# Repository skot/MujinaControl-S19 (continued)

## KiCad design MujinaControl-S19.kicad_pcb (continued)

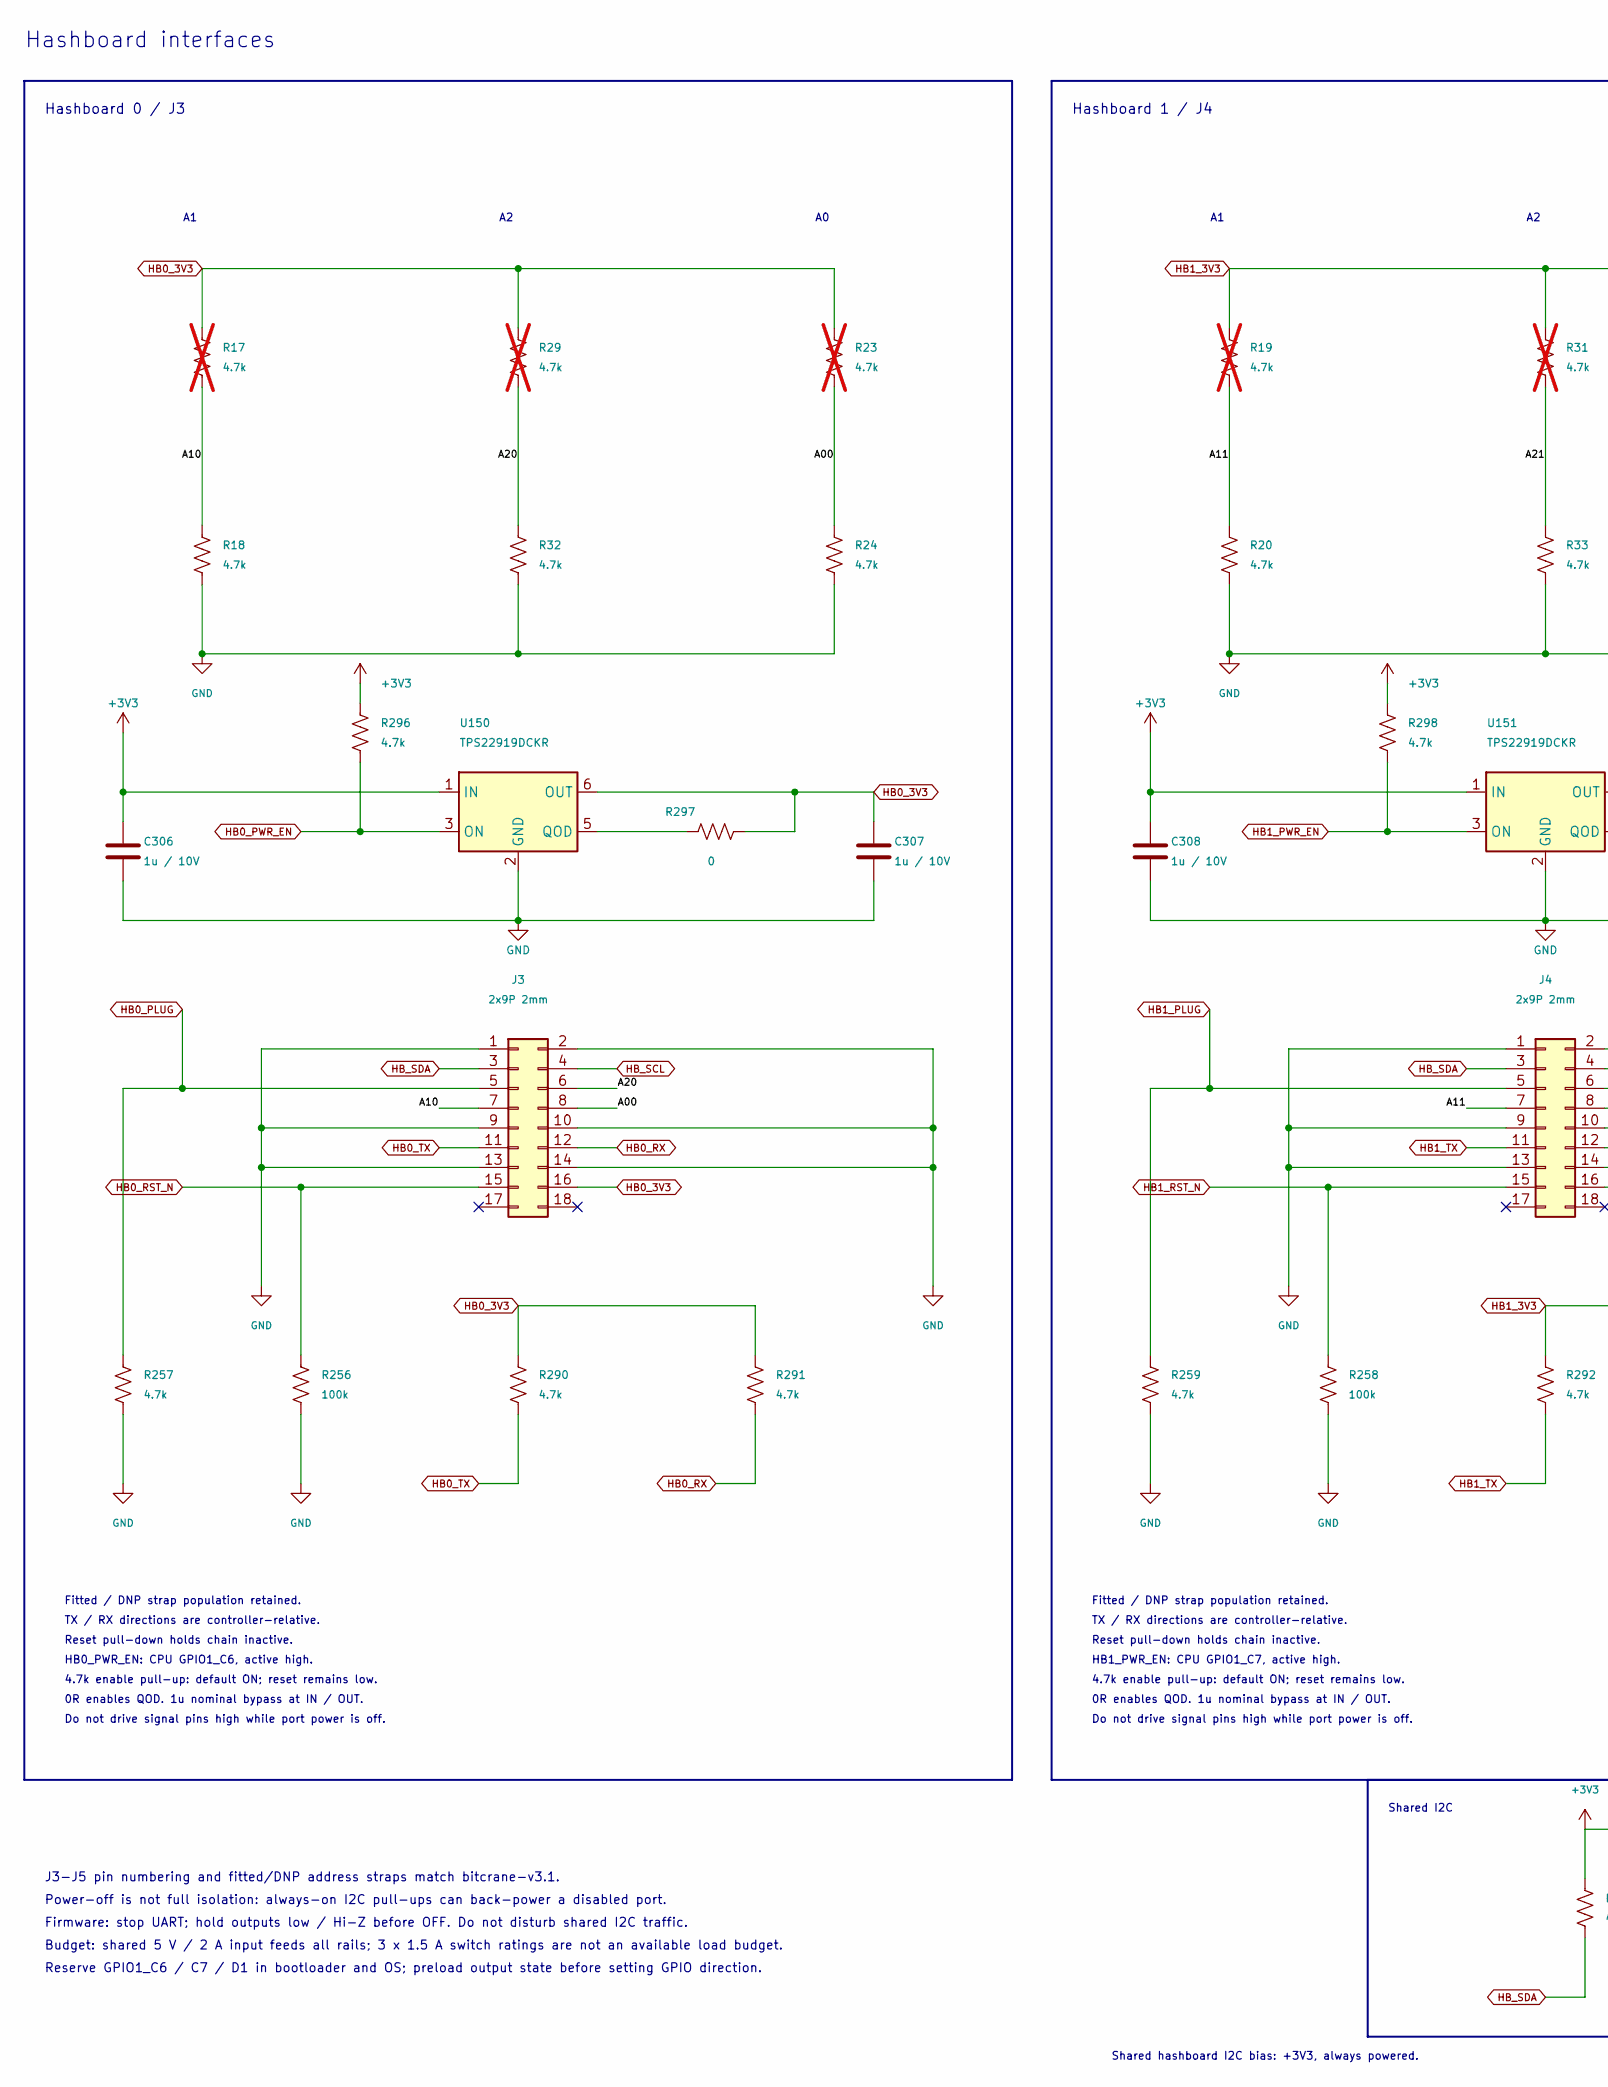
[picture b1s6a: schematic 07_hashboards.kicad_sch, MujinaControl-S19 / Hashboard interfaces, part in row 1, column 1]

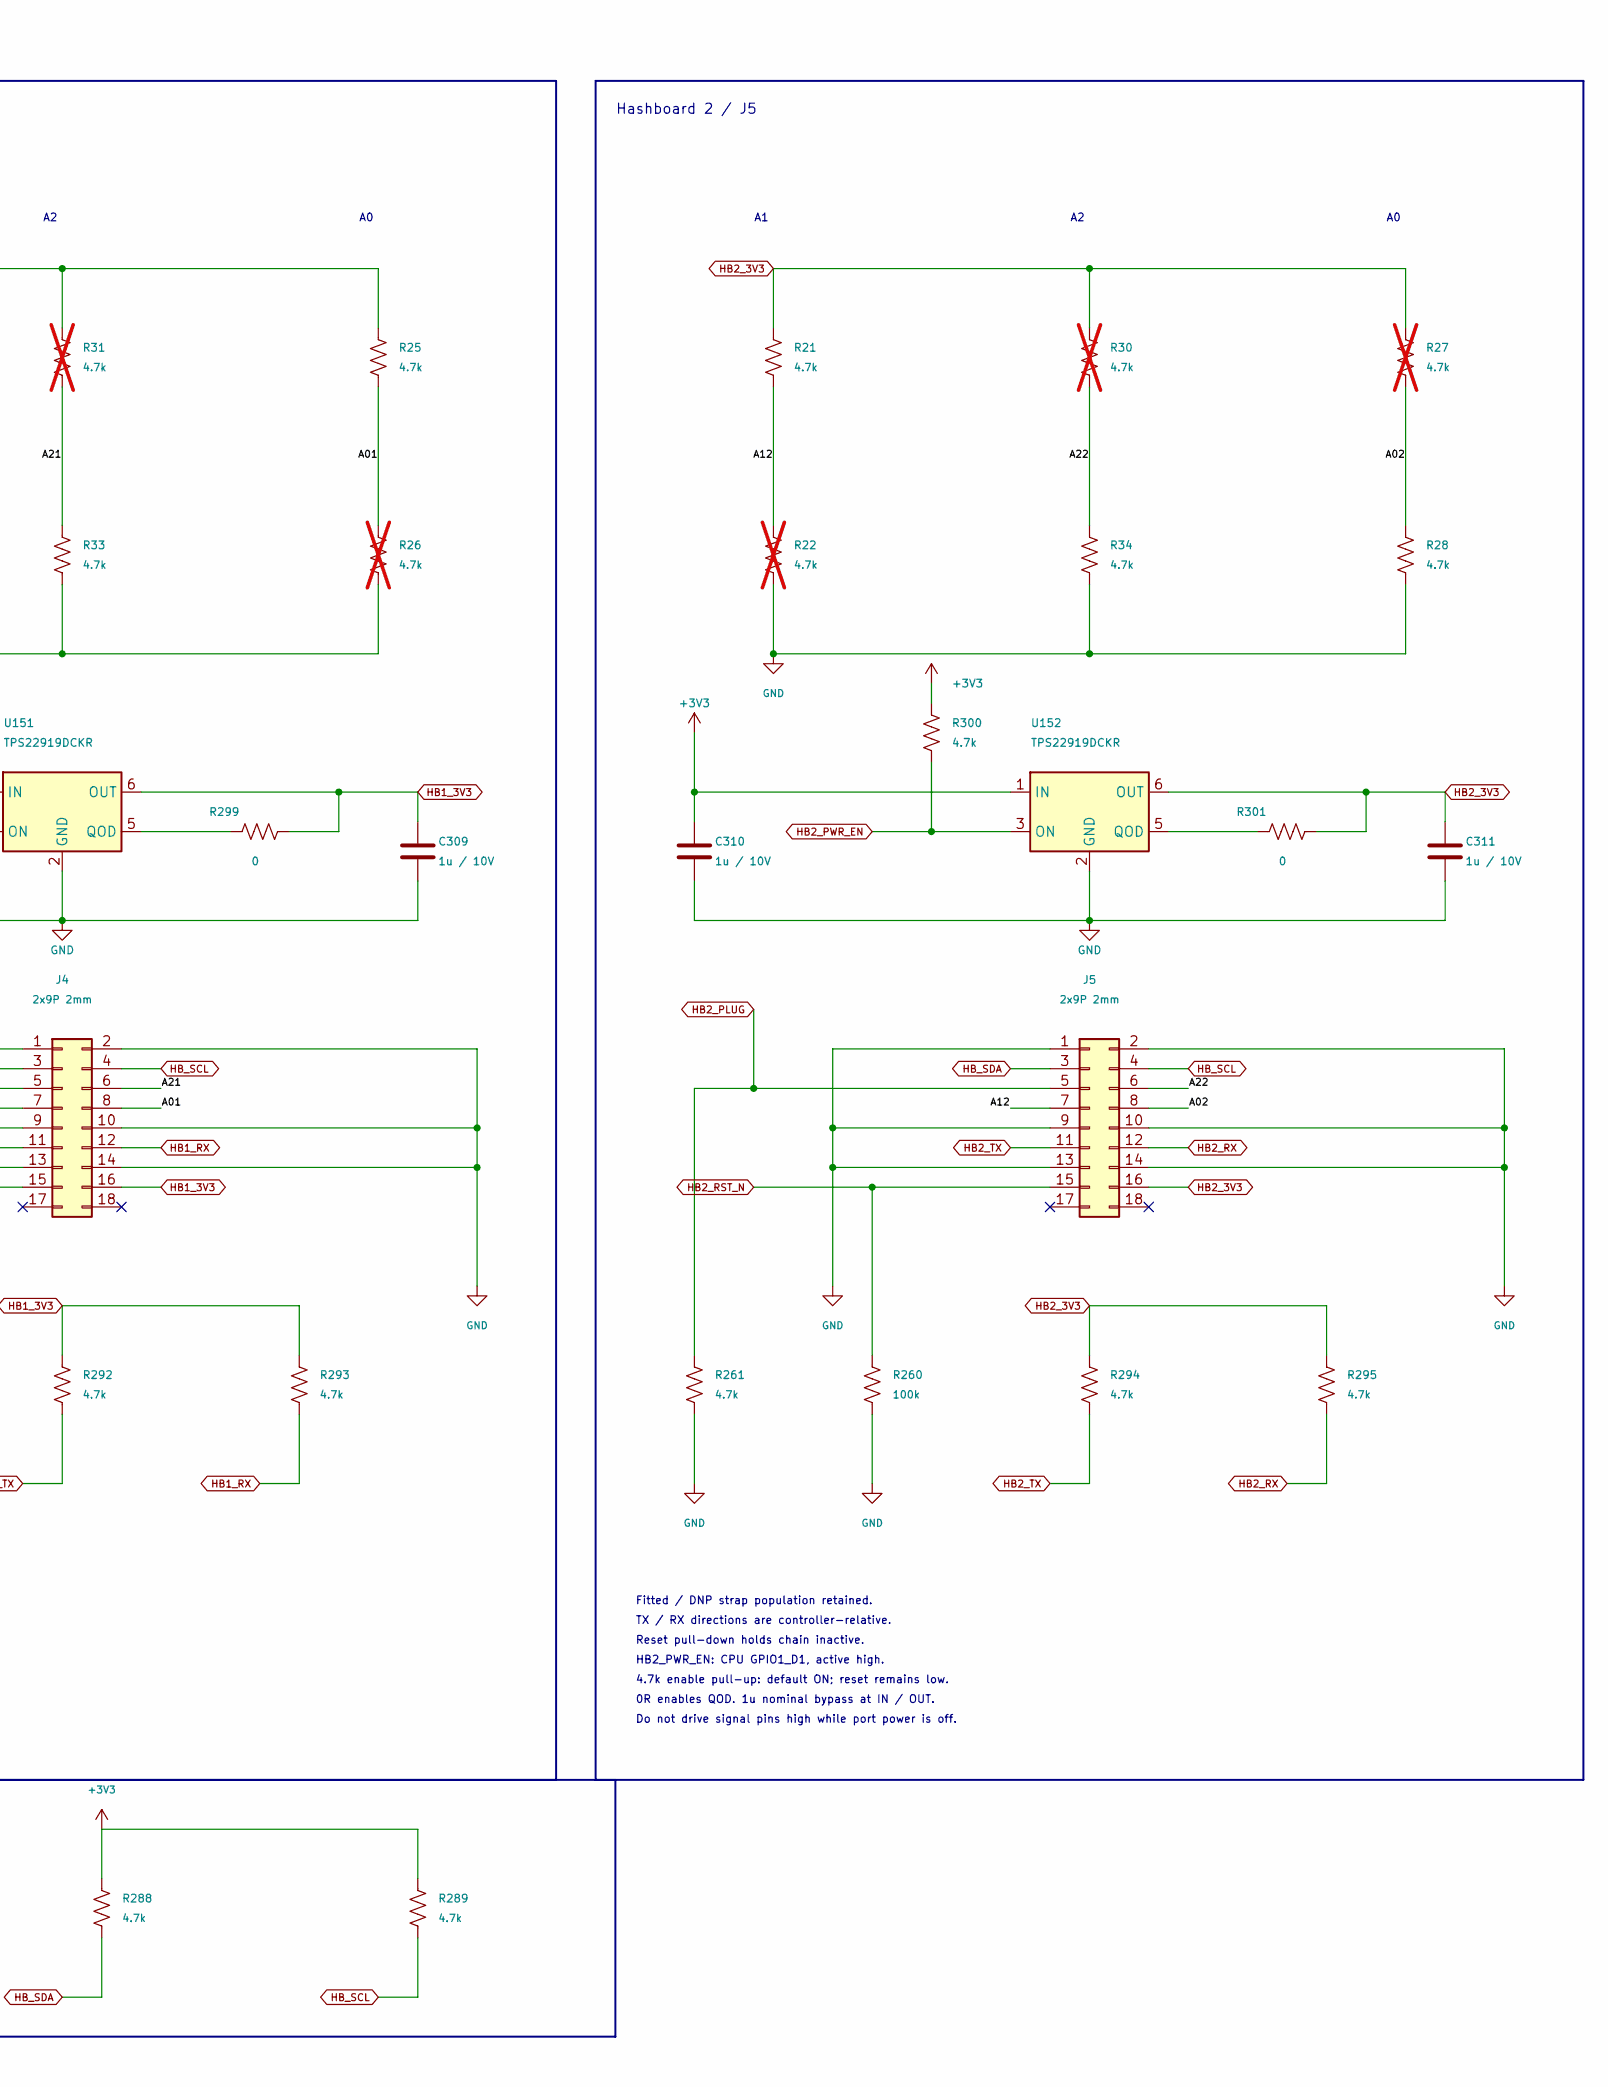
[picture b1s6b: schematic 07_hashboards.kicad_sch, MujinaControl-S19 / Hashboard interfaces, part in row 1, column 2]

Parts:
C306, C307, C308, C309, C310, C311: 1u / 10V; C_0402_1005Metric; MPN CL05A105KA5NQNC; LCSC C52923
J3, J4, J5: 2x9P 2mm; CONN-TH_X2026WV-2-09D-46SN; MPN X2026WV-2x09D-46SN; LCSC C437089
R17, R19, R22, R23, R26, R27, R29, R30, R31: 4.7k; R_0402_1005Metric; MPN 0402WGF4701TCE; LCSC C25900; not fitted
R18, R20, R21, R24, R25, R28, R32, R33, R34, R257, R259, R261, R288, R289, R290, R291, R292, R293, R294, R295, R296, R298, R300: 4.7k; R_0402_1005Metric; MPN 0402WGF4701TCE; LCSC C25900
R256, R258, R260: 100k; R_0402_1005Metric; MPN 0402WGF1003TCE; LCSC C25741
R297, R299, R301: 0; R_0402_1005Metric; MPN 0402WGF0000TCE; LCSC C17168
U150, U151, U152: TPS22919DCKR; SOT-363_SC-70-6; MPN TPS22919DCKR; LCSC C2149796

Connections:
+3V3: C306.1, C308.1, C310.1, R288.1, R289.1, R296.1, R298.1, R300.1, U150.1 (IN), U151.1 (IN), U152.1 (IN); also elsewhere on the board
/Three hashboard interfaces/A00: J3.8, R23.2, R24.1
/Three hashboard interfaces/A01: J4.8, R25.2, R26.1
/Three hashboard interfaces/A02: J5.8, R27.2, R28.1
/Three hashboard interfaces/A10: J3.7, R17.2, R18.1
/Three hashboard interfaces/A11: J4.7, R19.2, R20.1
/Three hashboard interfaces/A12: J5.7, R21.2, R22.1
/Three hashboard interfaces/A20: J3.6, R29.2, R32.1
/Three hashboard interfaces/A21: J4.6, R31.2, R33.1
/Three hashboard interfaces/A22: J5.6, R30.2, R34.1
GND: C306.2, C307.2, C308.2, C309.2, C310.2, C311.2, J3.1, J3.2, J3.9, J3.10, J3.13, J3.14, J4.1, J4.2, J4.9, J4.10, J4.13, J4.14, J5.1, J5.2, J5.9, J5.10, J5.13, J5.14, R18.2, R20.2, R22.2, R24.2, R26.2, R28.2, R32.2, R33.2, R34.2, R256.2, R257.2, R258.2, R259.2, R260.2, R261.2, U150.2 (GND), U151.2 (GND), U152.2 (GND); also elsewhere on the board
HB0_3V3: C307.1, J3.16, R17.1, R23.1, R29.1, R290.1, R291.1, R297.2, U150.6 (OUT)
HB0_PLUG: J3.5, R257.1; also elsewhere on the board
HB0_PWR_EN: R296.2, U150.3 (ON); also elsewhere on the board
HB0_RST_N: J3.15, R256.1; also elsewhere on the board
HB0_RX: J3.12, R291.2; also elsewhere on the board
HB0_TX: J3.11, R290.2; also elsewhere on the board
HB1_3V3: C309.1, J4.16, R19.1, R25.1, R31.1, R292.1, R293.1, R299.2, U151.6 (OUT)
HB1_PLUG: J4.5, R259.1; also elsewhere on the board
HB1_PWR_EN: R298.2, U151.3 (ON); also elsewhere on the board
HB1_RST_N: J4.15, R258.1; also elsewhere on the board
HB1_RX: J4.12, R293.2; also elsewhere on the board
HB1_TX: J4.11, R292.2; also elsewhere on the board
HB2_3V3: C311.1, J5.16, R21.1, R27.1, R30.1, R294.1, R295.1, R301.2, U152.6 (OUT)
HB2_PLUG: J5.5, R261.1; also elsewhere on the board
HB2_PWR_EN: R300.2, U152.3 (ON); also elsewhere on the board
HB2_RST_N: J5.15, R260.1; also elsewhere on the board
HB2_RX: J5.12, R295.2; also elsewhere on the board
HB2_TX: J5.11, R294.2; also elsewhere on the board
HB_SCL: J3.4, J4.4, J5.4, R289.2; also elsewhere on the board
HB_SDA: J3.3, J4.3, J5.3, R288.2; also elsewhere on the board
unnamed: R297.1, U150.5 (QOD)
unnamed: R299.1, U151.5 (QOD)
unnamed: R301.1, U152.5 (QOD)

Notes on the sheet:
Fitted / DNP strap population retained.
Hashboard 1 / J4
Reset pull-down holds chain inactive.
HB0_PWR_EN: CPU GPIO1_C6, active high.
Power-off is not full isolation: always-on I2C pull-ups can back-power a disabled port.
TX / RX directions are controller-relative.
Do not drive signal pins high while port power is off.
HB1_PWR_EN: CPU GPIO1_C7, active high.
J3-J5 pin numbering and fitted/DNP address straps match bitcrane-v3.1.
4.7k enable pull-up: default ON; reset remains low.
0R enables QOD. 1u nominal bypass at IN / OUT.
Hashboard 0 / J3
Shared I2C
Hashboard 2 / J5
Hashboard interfaces
HB2_PWR_EN: CPU GPIO1_D1, active high.
Budget: shared 5 V / 2 A input feeds all rails; 3 x 1.5 A switch ratings are not an available load budget.
Reserve GPIO1_C6 / C7 / D1 in bootloader and OS; preload output state before setting GPIO direction.
Firmware: stop UART; hold outputs low / Hi-Z before OFF. Do not disturb shared I2C traffic.
Shared hashboard I2C bias: +3V3, always powered.

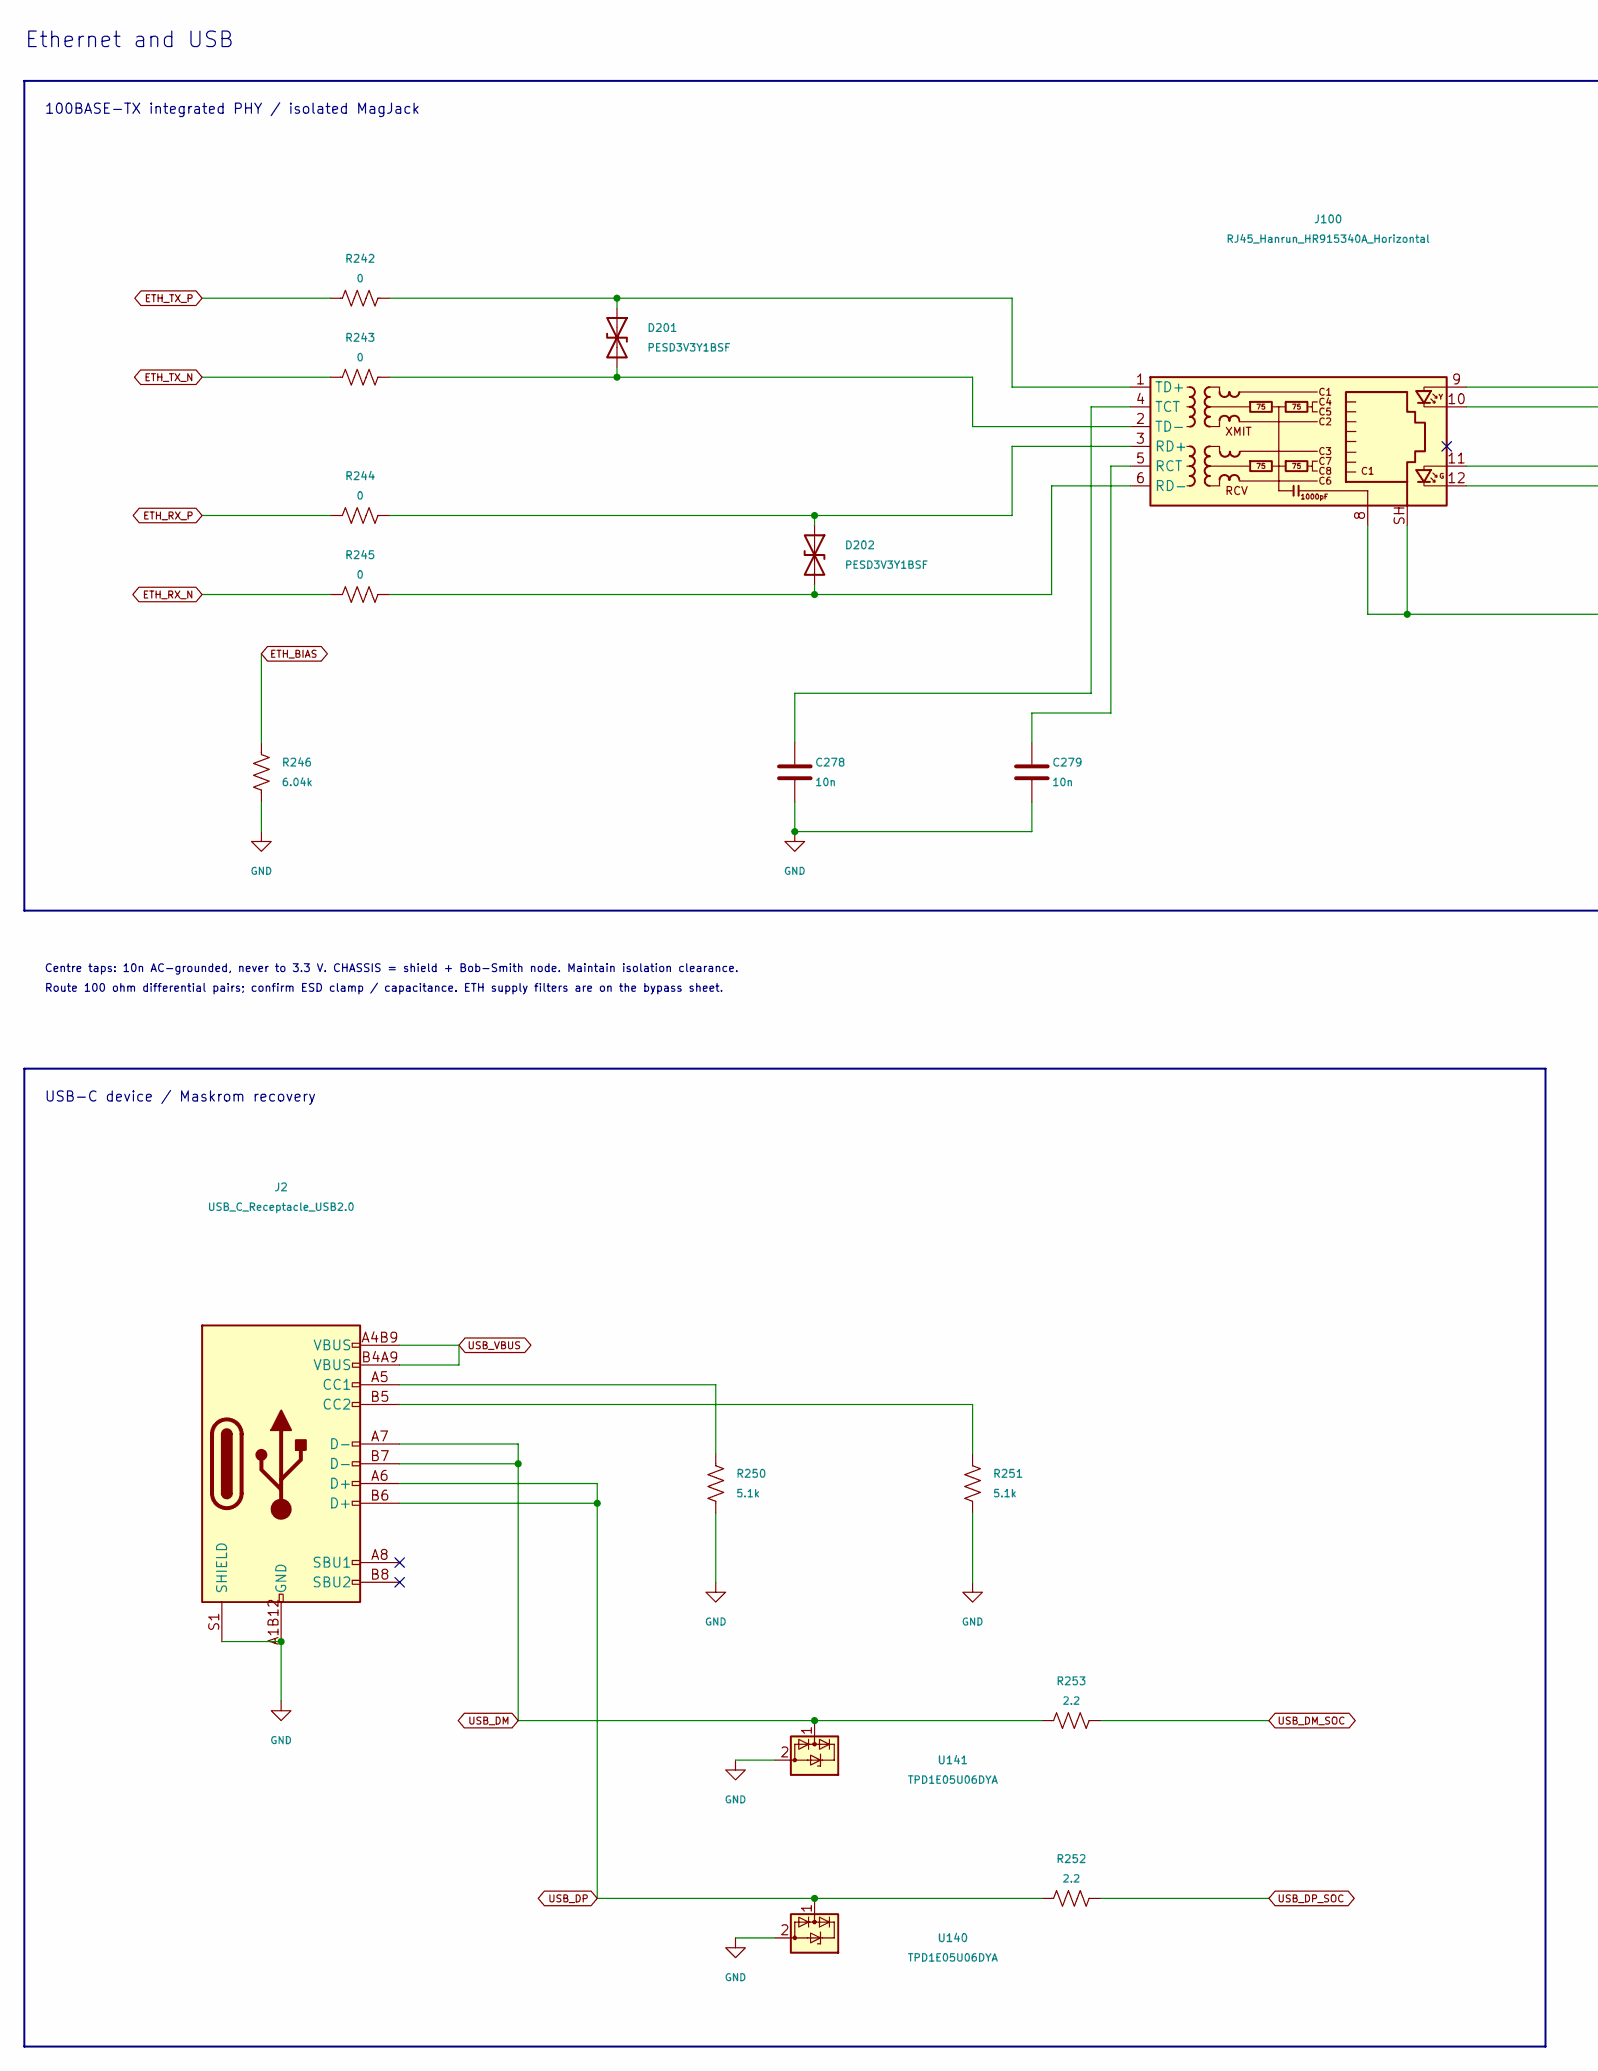
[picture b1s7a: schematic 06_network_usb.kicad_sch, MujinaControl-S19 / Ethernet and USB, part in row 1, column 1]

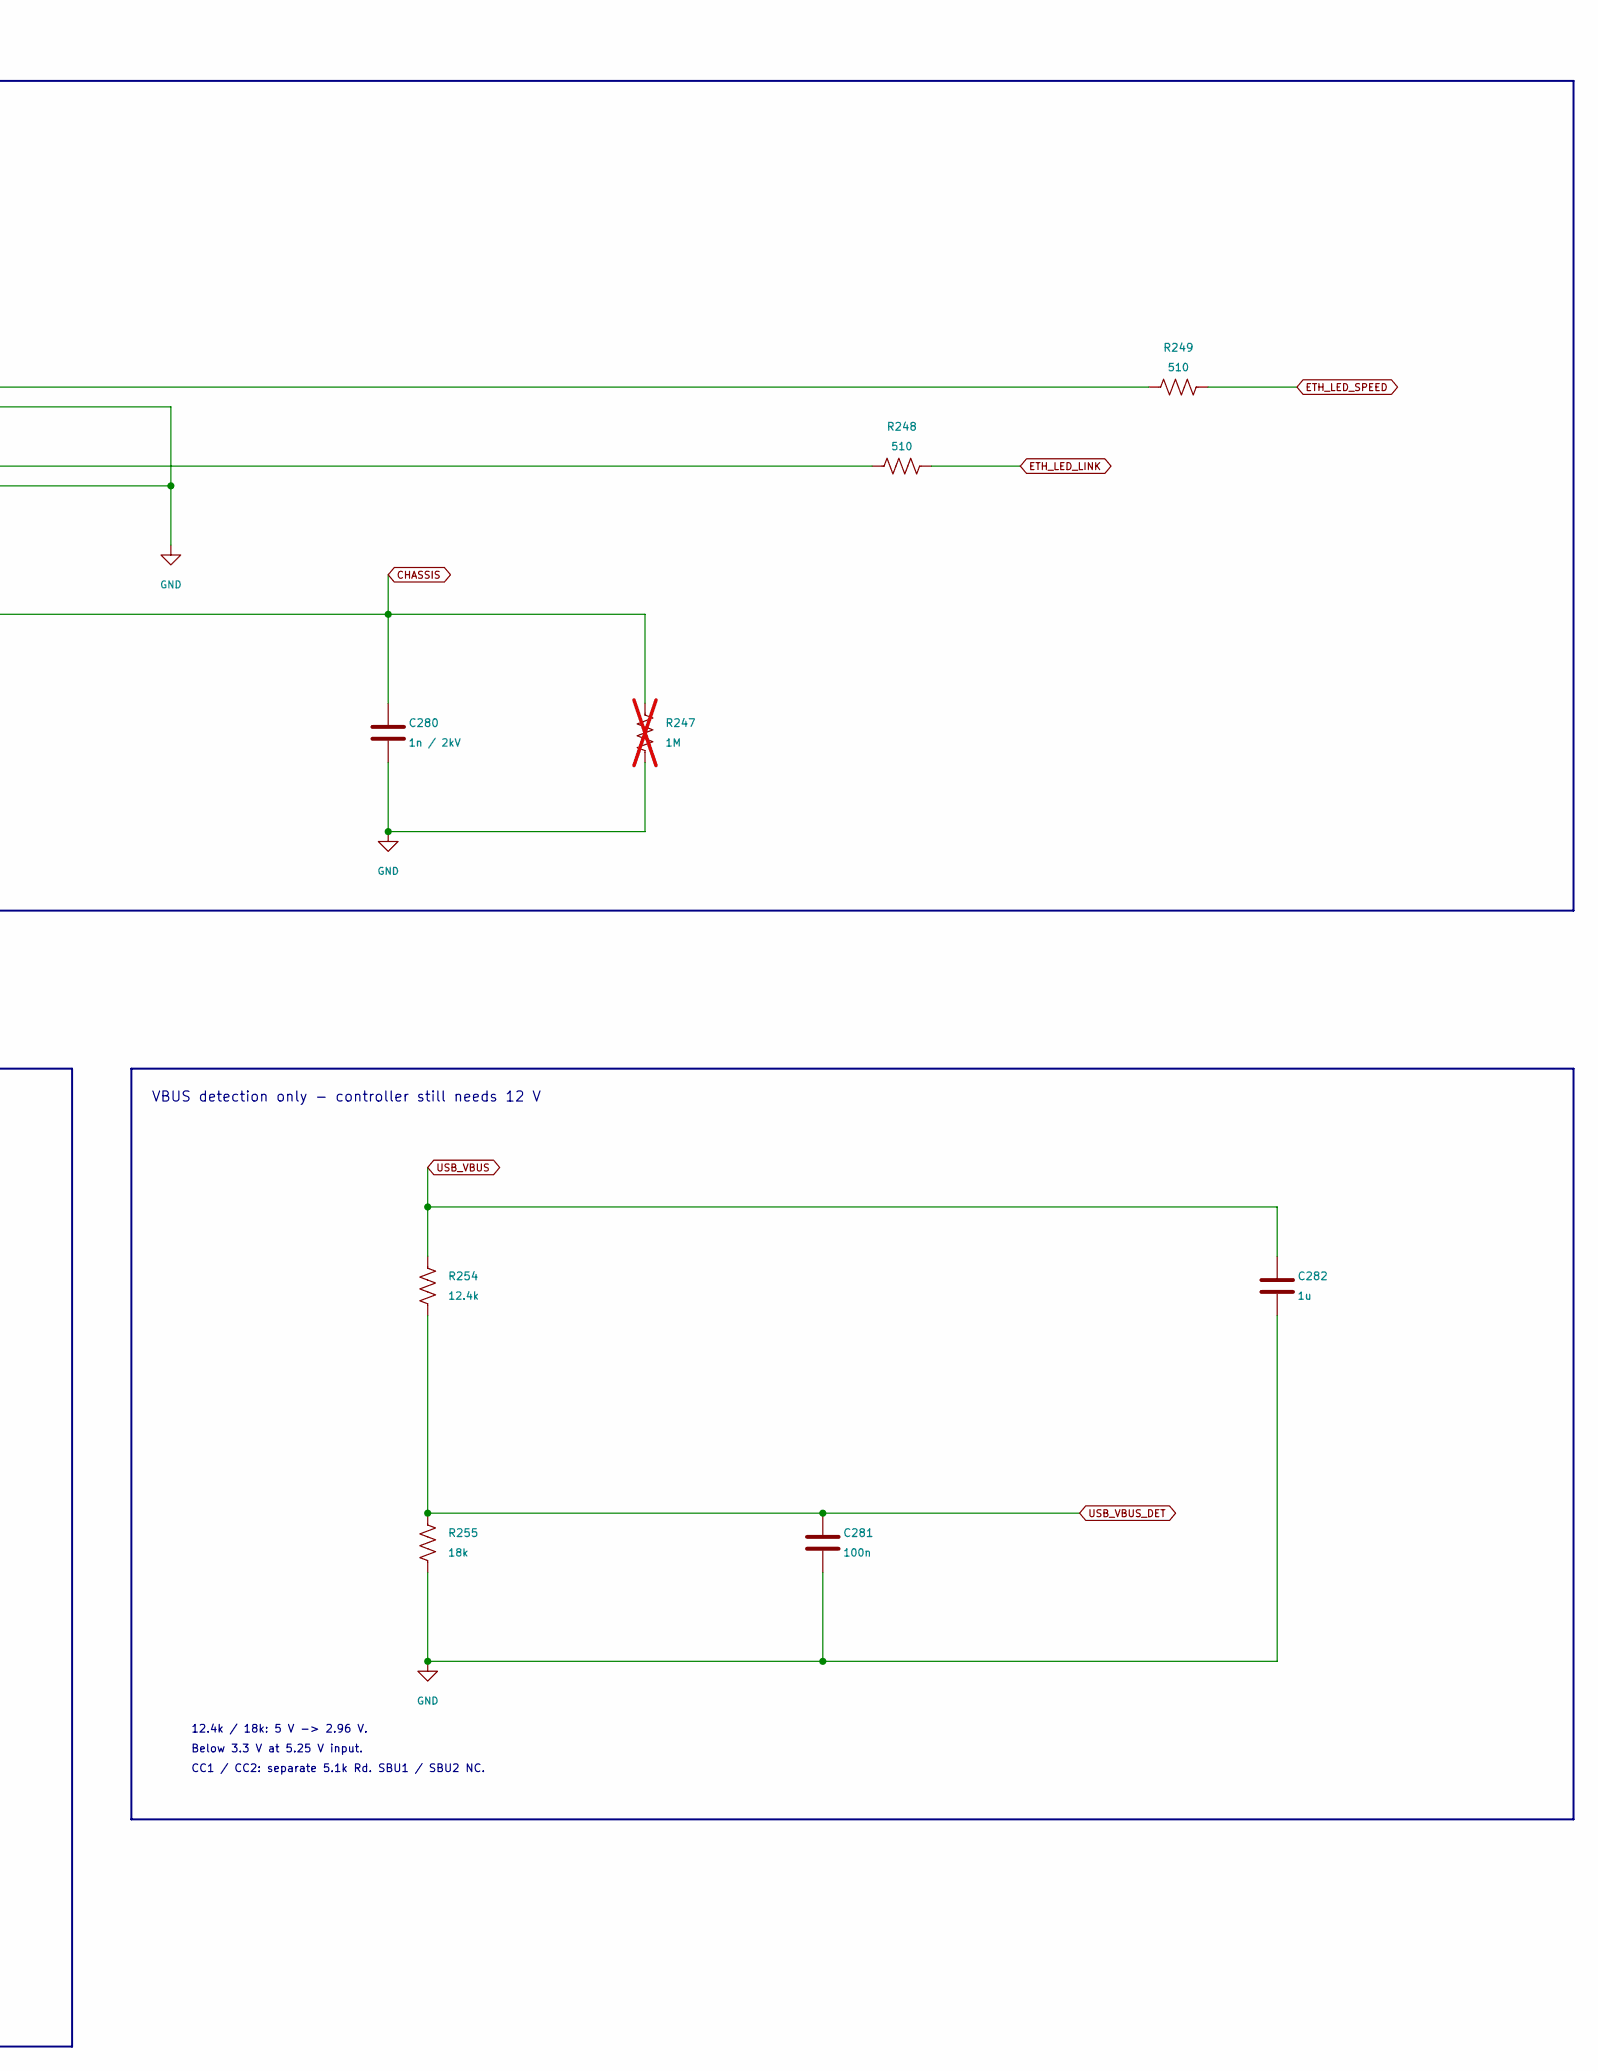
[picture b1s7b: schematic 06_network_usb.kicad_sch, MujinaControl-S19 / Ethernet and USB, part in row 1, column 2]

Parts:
C278, C279: 10n; C_0402_1005Metric; MPN CL05B103KB5NNNC; LCSC C15195
C280: 1n / 2kV; C_1808_4520Metric; MPN C1808C102KGRACTU; LCSC C2167485
C281: 100n; C_0402_1005Metric; MPN CL05B104KO5NNNC; LCSC C1525
C282: 1u; C_0402_1005Metric; MPN CL05A105KA5NQNC; LCSC C52923
D201, D202: PESD3V3Y1BSF; Nexperia_DSN0603-2_0.6x0.3mm_P0.4mm; MPN PESD3V3Y1BSFYL; LCSC C552535
J2: USB_C_Receptacle_USB2.0; USB_C_Receptacle_GCT_USB4105-xx-A_16P_TopMnt_Horizontal; MPN USB4105-GF-A; LCSC C3020560
J100: RJ45_Hanrun_HR915340A_Horizontal; MPN HR915340A; LCSC C2760325
R242, R243, R244, R245: 0; R_0402_1005Metric; MPN 0402WGF0000TCE; LCSC C17168
R246: 6.04k; R_0402_1005Metric; MPN RC0402FR-076K04L; LCSC C97819
R247: 1M; R_0402_1005Metric; MPN 0402WGF1004TCE; LCSC C26083; not fitted
R248, R249: 510; R_0402_1005Metric; MPN 0402WGF5100TCE; LCSC C25123
R250, R251: 5.1k; R_0402_1005Metric; MPN 0402WGF5101TCE; LCSC C25905
R252, R253: 2.2; R_0402_1005Metric; MPN RC0402FR-072R2L; LCSC C327251
R254: 12.4k; R_0402_1005Metric; MPN RC0402FR-0712K4L; LCSC C138060
R255: 18k; R_0402_1005Metric; MPN 0402WGF1802TCE; LCSC C25762
U140, U141: TPD1E05U06DYA; D_SOD-523; MPN TPD1E05U06DYA; LCSC C3702980

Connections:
CHASSIS: C280.1, J100.8, J100.SH, R247.1
ETH_BIAS: R246.1; also elsewhere on the board
ETH_LED_LINK: R248.1; also elsewhere on the board
ETH_LED_SPEED: R249.1; also elsewhere on the board
ETH_RX_N: R245.1; also elsewhere on the board
ETH_RX_P: R244.1; also elsewhere on the board
ETH_TX_N: R243.1; also elsewhere on the board
ETH_TX_P: R242.1; also elsewhere on the board
GND: C278.2, C279.2, C280.2, C281.2, C282.2, J2.A1B12 (GND), J2.B1A12 (GND), J2.S1 (SHIELD), J100.10, J100.12, R246.2, R247.2, R250.2, R251.2, R255.2, U140.2 (GND), U141.2 (GND); also elsewhere on the board
unnamed: D201.1 (A1), J100.1 (TD+), R242.2
unnamed: D201.2 (A2), J100.2 (TD-), R243.2
unnamed: D202.1 (A1), J100.3 (RD+), R244.2
unnamed: D202.2 (A2), J100.6 (RD-), R245.2
unnamed: J2.A5 (CC1), R250.1
unnamed: J2.B5 (CC2), R251.1
unnamed: J100.9, R249.2
unnamed: J100.11, R248.2
unnamed: C279.1, J100.5 (RCT)
unnamed: C278.1, J100.4 (TCT)
USB_DM: J2.A7 (D-), J2.B7 (D-), R253.2, U141.1 (I/O)
USB_DM_SOC: R253.1; also elsewhere on the board
USB_DP: J2.A6 (D+), J2.B6 (D+), R252.2, U140.1 (I/O)
USB_DP_SOC: R252.1; also elsewhere on the board
USB_VBUS: C282.1, J2.A4B9 (VBUS), J2.B4A9 (VBUS), R254.1
USB_VBUS_DET: C281.1, R254.2, R255.1; also elsewhere on the board

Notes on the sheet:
Ethernet and USB
100BASE-TX integrated PHY / isolated MagJack
12.4k / 18k: 5 V -> 2.96 V.
Centre taps: 10n AC-grounded, never to 3.3 V. CHASSIS = shield + Bob-Smith node. Maintain isolation clearance.
Route 100 ohm differential pairs; confirm ESD clamp / capacitance. ETH supply filters are on the bypass sheet.
Below 3.3 V at 5.25 V input.
CC1 / CC2: separate 5.1k Rd. SBU1 / SBU2 NC.
VBUS detection only - controller still needs 12 V
USB-C device / Maskrom recovery
